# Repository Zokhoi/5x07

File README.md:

# Project 5x07

A low profile ortholinear split keyboard with per-key RGB.

This is a project that began as my first adventure into PCB and keyboard design.

## Parts required

**This table is for one PCB. You need double of this for both hands.**

| Part                                                                                                                                                   | Part Details                                                                                                                                                                        | Quantity | Notes                                       |
| ------------------------------------------------------------------------------------------------------------------------------------------------------ | ----------------------------------------------------------------------------------------------------------------------------------------------------------------------------------- | -------- | ------------------------------------------- |
| [ATmega32u4-AU](https://item.taobao.com/item.htm?id=677430063008)                                                                                      | TQFP-44                                                                                                                                                                             | 1        |                                             |
| [Korean Hroparts Elec TYPE-C-31-M-12](https://www.lcsc.com/product-detail/USB-Type-C_Korean-Hroparts-Elec-TYPE-C-31-M-12_C165948.html)                 |                                                                                                                                                                                     | 1        |                                             |
| [Korean Hroparts ELEC PJ-3200B-4A TRRS Jack](https://www.lcsc.com/product-detail/Audio-Video-Connectors_Korean-Hroparts-Elec-PJ-3200B-4A_C136687.html) |                                                                                                                                                                                     | 1        | For split keyboard connection               |
| [SK6812 Mini-E Reverse Mount LED](https://item.taobao.com/item.htm?id=669061805532)                                                                    |                                                                                                                                                                                     | 35       |                                             |
| [16MHz 3225 SMD Crystal](https://lcsc.com/product-detail/Crystals_Seiko-Epson-X1E000021061300_C255909.html)                                            |                                                                                                                                                                                     | 1        |                                             |
| [PRTR5V0U2X](https://lcsc.com/product-detail/Diodes-ESD_Nexperia-PRTR5V0U2X-215_C12333.html)                                                           | SOT143B                                                                                                                                                                             |          | For ESD protection                          |
| [SKQG push button switch](https://lcsc.com/product-detail/Tactile-Switches_ALPSALPINE-SKQGAFE010_C202424.html)                                         |                                                                                                                                                                                     | 1        | For reset circuit                           |
| 0608/2012 SMD Resistor                                                                                                                                 | [10kΩ](https://lcsc.com/product-detail/Chip-Resistor-Surface-Mount_Viking-Tech-AR05BTCW1002_C316200.html)                                                                           | 3        | For MCU HWB and TRRS jack (i2c)             |
|                                                                                                                                                        | [500Ω](https://lcsc.com/product-detail/Chip-Resistor-Surface-Mount_Viking-Tech-ARG05BTC5000_C2828711.html)                                                                          | 1        | For keyboard LED                            |
|                                                                                                                                                        | [5.1kΩ](https://lcsc.com/product-detail/Chip-Resistor-Surface-Mount_Viking-Tech-AR05DTCW5101_C319564.html)                                                                          | 2        | For USB-C CC                                |
|                                                                                                                                                        | [22Ω](https://lcsc.com/product-detail/Chip-Resistor-Surface-Mount_Viking-Tech-ARG05BTC0220_C309084.html)                                                                            | 2        | For USB-C data                              |
|                                                                                                                                                        | [330Ω](https://lcsc.com/product-detail/Chip-Resistor-Surface-Mount_Viking-Tech-ARG05BTC3300_C2984456.html)                                                                          | 1        | For reset circuit                           |
| 1206/3212 SMD Fuse                                                                                                                                     | [500mA](https://lcsc.com/product-detail/PTC-Resettable-Fuses_TECHFUSE-nSMD025-24V_C70069.html)                                                                                      | 1        |                                             |
| Diodes                                                                                                                                                 | [1N4148](https://lcsc.com/product-detail/Switching-Diode_MCC-Micro-Commercial-Components-1N4148W-TP_C77978.html) or SMD                                                             | 35       | For keyboard matrix                         |
|                                                                                                                                                        | [Schottky](https://lcsc.com/product-detail/Schottky-Barrier-Diodes-SBD_Shikues-B5817WL_C122853.html)                                                                                | 1        | For USB-C power                             |
| 0805 SMD Capacitors                                                                                                                                    | [22 pF](https://lcsc.com/product-detail/Multilayer-Ceramic-Capacitors-MLCC-SMD-SMT_Samsung-Electro-Mechanics-CL21C220JCANNNC_C165459.html)                                          | 2        | For crystal                                 |
|                                                                                                                                                        | [1 uF](https://lcsc.com/product-detail/Multilayer-Ceramic-Capacitors-MLCC-SMD-SMT_Samsung-Electro-Mechanics_CL21B105KAFNNNE_Samsung-Electro-Mechanics-CL21B105KAFNNNE_C116352.html) | 1        | For MCU UCAP                                |
|                                                                                                                                                        | [10 uF](https://lcsc.com/product-detail/Multilayer-Ceramic-Capacitors-MLCC-SMD-SMT_SAMSUNG_CL21B106KOQNNNE_10uF-106-10-16V_C95841.html)                                             | 1        | For decoupling                              |
|                                                                                                                                                        | [0.1 uF](https://lcsc.com/product-detail/Multilayer-Ceramic-Capacitors-MLCC-SMD-SMT_SAMSUNG_CL21B104JBCNNNC_100nF-104-5-50V_C62912.html)                                            | 4        | For decoupling                              |
| M2 screws                                                                                                                                              | >=3mm                                                                                                                                                                               | 8        | For bottom plate, length for reference only |
| M2 standoff                                                                                                                                            | 3mm                                                                                                                                                                                 | 4        | For bottom plate, length for reference only |

## Board details

Fabrication gerber files are in `./PCB/gerber` directory.

103.188 mm H x 168.275 mm W <br />
2 layers <br />
Unleaded HASL or ENIG <br />
1.6mm thick <br />
white on black

## Assembly instructions

The images below are PCBs for v3.

The board is designed to be reversible. You can flip the PCB to the other side to serve as the other half.

The parts that are mountable on both sides of the PCB are the type C port, the TRRS jack, the reset button and the key matrix (switch, LED, diode).

The side for mounting type C port and TRRS jack is up to your will. The reset button should always face up for ease of access. The LEDs for keyboard are reverse mounted. Key diodes should be on the underside.

As one side would have its electrionic components mostly facing down, you should lift the split halves up to avoid shorting. If you have leftover boards from ordering in batch amounts, it is possible to use them as bottom plates using M2 screws and standoffs. 

For information, the shortest M2 standoffs I can find are 3mm in length, the type C port is 3.2mm high, and the TRRS jack is 5mm high (the outer plastic ring might be 5.6mm high). If you decide to put the type C port and TRRS jack on the top side, you can have the standoff as short as just higher than the electronic components on the board.

## Build instructions

By default the keyboard is set to use EEPROM handedness check, this means that
for the first time for both halves the following commands need to be used:

```bash
make 5x07:default:dfu-split-left
make 5x07:default:dfu-split-right
```

afterwards the end part can be dropped when flashing again.

For v3 and below there is no VBUS detection, so USB activity detection must be used for split master detection if you do not want to hardcode the master half. <br />
V3.1 onwards has VBUS detection and you can use it normally.

## CAUTIONS

I couldn't for the life of me figure out how to stably enable the per key RGB, so use at your own risk.

Some problems that I encountered were:

* RHS board (using EEPROM flags) could have RGB lights on in QMK, but then it disconnects if the mode switches from the static gradient to static solid color.
* RHS board can change modes between different static gradients if its hue/saturation/value are turned down first.
* LHS board disconnects from computer immediately after connection when RGB is enabled. If the USB is connected to RHS board and LHS is connected to RHS via i2c, it would drag both halves down with the disconnection. After disconnection, the RGB lights start to flicker.
* RHS board would also display random disconnection behavior if the hsv are changed too fast.

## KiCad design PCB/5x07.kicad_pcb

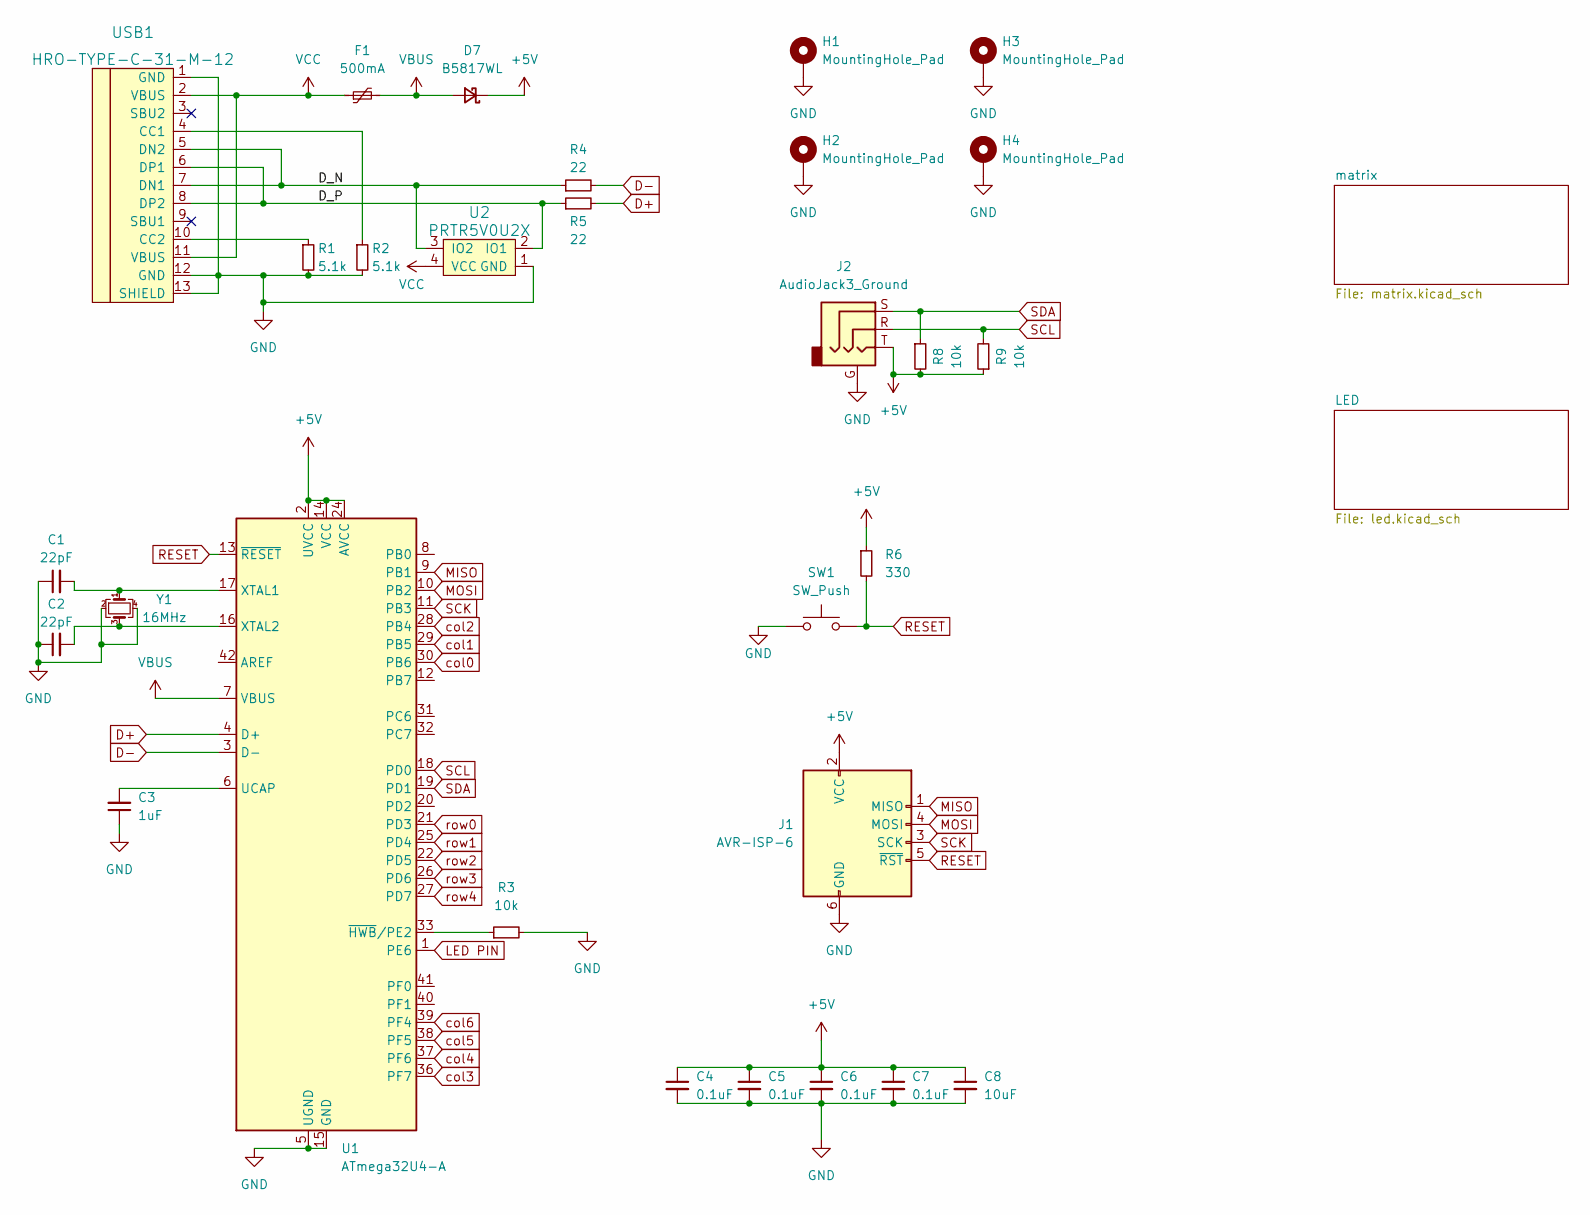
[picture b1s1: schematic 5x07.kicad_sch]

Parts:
C1, C2: 22pF; C_0805_2012Metric_Pad1.18x1.45mm_HandSolder
C3: 1uF; C_0805_2012Metric_Pad1.18x1.45mm_HandSolder
C4, C5, C6, C7: 0.1uF; C_0805_2012Metric_Pad1.18x1.45mm_HandSolder
C8: 10uF; C_0805_2012Metric_Pad1.18x1.45mm_HandSolder
D7: B5817WL; D_SOD-123F
F1: 500mA; Fuse_1206_3216Metric_Pad1.42x1.75mm_HandSolder
H1, H2, H3, H4: MountingHole_Pad; Generic-Mounthole
J1: AVR-ISP-6; Reset_Pretty
J2: AudioJack3_Ground; PJ-3200B-4A-Reversible-Mini
R1, R2: 5.1k; R_0805_2012Metric_Pad1.20x1.40mm_HandSolder
R3, R8, R9: 10k; R_0805_2012Metric_Pad1.20x1.40mm_HandSolder
R4, R5: 22; R_0805_2012Metric_Pad1.20x1.40mm_HandSolder
R6: 330; R_0805_2012Metric_Pad1.20x1.40mm_HandSolder
SW1: SW_Push; SW_SPST_SKQG_WithStem_Reversible
U1: ATmega32U4-A; TQFP-44_10x10mm_P0.8mm
U2: PRTR5V0U2X; SOT143B
USB1: HRO-TYPE-C-31-M-12; HRO-TYPE-C-31-M-12-HandSoldering-Reversible
Y1: 16MHz; Crystal_SMD_3225-4Pin_3.2x2.5mm_HandSoldering

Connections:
+5V: C4.1, C5.1, C6.1, C7.1, C8.1, D7.1 (K), J1.2 (VCC), J2.T, R6.1, R8.2, R9.1, U1.2 (UVCC), U1.14 (VCC), U1.24 (AVCC), U1.34 (VCC), U1.44 (AVCC); also elsewhere on the board
/D_N: R4.1, U2.3 (IO2), USB1.5 (DN2), USB1.7 (DN1)
/D_P: R5.1, U2.2 (IO1), USB1.6 (DP1), USB1.8 (DP2)
D+: R5.2, U1.4 (D+)
D-: R4.2, U1.3 (D-)
GND: C1.1, C2.1, C3.1, C4.2, C5.2, C6.2, C7.2, C8.2, H1.1, H2.1, H3.1, H4.1, J1.6 (GND), J2.G, R1.2, R2.2, R3.2, SW1.1, U1.5 (UGND), U1.15 (GND), U1.23 (GND), U1.35 (GND), U1.43 (GND), U2.1 (GND), USB1.1 (GND), USB1.12 (GND), USB1.13 (SHIELD), Y1.2, Y1.4; also elsewhere on the board
LED PIN: U1.1 (PE6); also elsewhere on the board
MISO: J1.1 (MISO), U1.9 (PB1)
MOSI: J1.4 (MOSI), U1.10 (PB2)
unnamed: C1.2, U1.17 (XTAL1), Y1.1
unnamed: C2.2, U1.16 (XTAL2), Y1.3
unnamed: C3.2, U1.6 (UCAP)
unnamed: R1.1, USB1.10 (CC2)
unnamed: R2.1, USB1.4 (CC1)
unnamed: R3.1, U1.33 (~HWB/PE2)
RESET: J1.5 (~RST), R6.2, SW1.2, U1.13 (~RESET)
SCK: J1.3 (SCK), U1.11 (PB3)
SCL: J2.R, R9.2, U1.18 (PD0)
SDA: J2.S, R8.1, U1.19 (PD1)
VCC: F1.1, U2.4 (VCC), USB1.2 (VBUS), USB1.11 (VBUS)
col0: U1.30 (PB6); also elsewhere on the board
col1: U1.29 (PB5); also elsewhere on the board
col2: U1.28 (PB4); also elsewhere on the board
col3: U1.36 (PF7); also elsewhere on the board
col4: U1.37 (PF6); also elsewhere on the board
col5: U1.38 (PF5); also elsewhere on the board
col6: U1.39 (PF4); also elsewhere on the board
row0: U1.21 (PD3); also elsewhere on the board
row1: U1.25 (PD4); also elsewhere on the board
row2: U1.22 (PD5); also elsewhere on the board
row3: U1.26 (PD6); also elsewhere on the board
row4: U1.27 (PD7); also elsewhere on the board

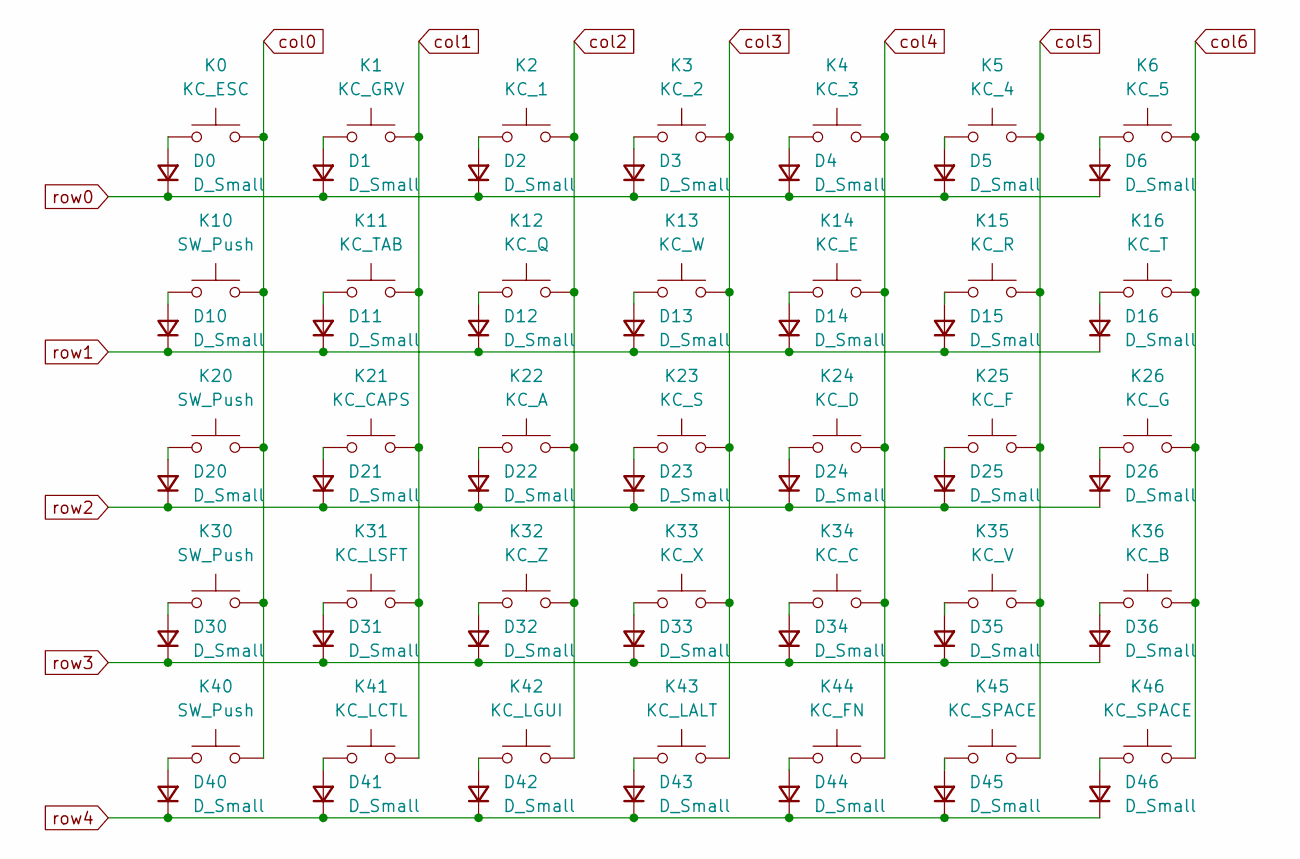
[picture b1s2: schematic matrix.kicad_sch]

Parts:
D0, D1, D2, D3, D4, D5, D6, D10, D11, D12, D13, D14, D15, D16, D20, D21, D22, D23, D24, D25, D26, D30, D31, D32, D33, D34, D35, D36, D40, D41, D42, D43, D44, D45, D46: D_Small; D_SOD-123-Reversible
K0: KC_ESC; SW_choc_1u_reversible
K1: KC_GRV; SW_choc_1u_reversible
K2: KC_1; SW_choc_1u_reversible
K3: KC_2; SW_choc_1u_reversible
K4: KC_3; SW_choc_1u_reversible
K5: KC_4; SW_choc_1u_reversible
K6: KC_5; SW_choc_1u_reversible
K10, K20, K30, K40: SW_Push; SW_choc_1u_reversible
K11: KC_TAB; SW_choc_1u_reversible
K12: KC_Q; SW_choc_1u_reversible
K13: KC_W; SW_choc_1u_reversible
K14: KC_E; SW_choc_1u_reversible
K15: KC_R; SW_choc_1u_reversible
K16: KC_T; SW_choc_1u_reversible
K21: KC_CAPS; SW_choc_1u_reversible
K22: KC_A; SW_choc_1u_reversible
K23: KC_S; SW_choc_1u_reversible
K24: KC_D; SW_choc_1u_reversible
K25: KC_F; SW_choc_1u_reversible
K26: KC_G; SW_choc_1u_reversible
K31: KC_LSFT; SW_choc_1u_reversible
K32: KC_Z; SW_choc_1u_reversible
K33: KC_X; SW_choc_1u_reversible
K34: KC_C; SW_choc_1u_reversible
K35: KC_V; SW_choc_1u_reversible
K36: KC_B; SW_choc_1u_reversible
K41: KC_LCTL; SW_choc_1u_reversible
K42: KC_LGUI; SW_choc_1u_reversible
K43: KC_LALT; SW_choc_1u_reversible
K44: KC_FN; SW_choc_1u_reversible
K45, K46: KC_SPACE; SW_choc_1u_reversible

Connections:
unnamed: D0.2 (A), K0.1
unnamed: D1.2 (A), K1.1
unnamed: D2.2 (A), K2.1
unnamed: D3.2 (A), K3.1
unnamed: D4.2 (A), K4.1
unnamed: D5.2 (A), K5.1
unnamed: D6.2 (A), K6.1
unnamed: D10.2 (A), K10.1
unnamed: D11.2 (A), K11.1
unnamed: D12.2 (A), K12.1
unnamed: D13.2 (A), K13.1
unnamed: D14.2 (A), K14.1
unnamed: D15.2 (A), K15.1
unnamed: D16.2 (A), K16.1
unnamed: D20.2 (A), K20.1
unnamed: D21.2 (A), K21.1
unnamed: D22.2 (A), K22.1
unnamed: D23.2 (A), K23.1
unnamed: D24.2 (A), K24.1
unnamed: D25.2 (A), K25.1
unnamed: D26.2 (A), K26.1
unnamed: D30.2 (A), K30.1
unnamed: D31.2 (A), K31.1
unnamed: D32.2 (A), K32.1
unnamed: D33.2 (A), K33.1
unnamed: D34.2 (A), K34.1
unnamed: D35.2 (A), K35.1
unnamed: D36.2 (A), K36.1
unnamed: D40.2 (A), K40.1
unnamed: D41.2 (A), K41.1
unnamed: D42.2 (A), K42.1
unnamed: D43.2 (A), K43.1
unnamed: D44.2 (A), K44.1
unnamed: D45.2 (A), K45.1
unnamed: D46.2 (A), K46.1
col0: K0.2, K10.2, K20.2, K30.2, K40.2; also elsewhere on the board
col1: K1.2, K11.2, K21.2, K31.2, K41.2; also elsewhere on the board
col2: K2.2, K12.2, K22.2, K32.2, K42.2; also elsewhere on the board
col3: K3.2, K13.2, K23.2, K33.2, K43.2; also elsewhere on the board
col4: K4.2, K14.2, K24.2, K34.2, K44.2; also elsewhere on the board
col5: K5.2, K15.2, K25.2, K35.2, K45.2; also elsewhere on the board
col6: K6.2, K16.2, K26.2, K36.2, K46.2; also elsewhere on the board
row0: D0.1 (K), D1.1 (K), D2.1 (K), D3.1 (K), D4.1 (K), D5.1 (K), D6.1 (K); also elsewhere on the board
row1: D10.1 (K), D11.1 (K), D12.1 (K), D13.1 (K), D14.1 (K), D15.1 (K), D16.1 (K); also elsewhere on the board
row2: D20.1 (K), D21.1 (K), D22.1 (K), D23.1 (K), D24.1 (K), D25.1 (K), D26.1 (K); also elsewhere on the board
row3: D30.1 (K), D31.1 (K), D32.1 (K), D33.1 (K), D34.1 (K), D35.1 (K), D36.1 (K); also elsewhere on the board
row4: D40.1 (K), D41.1 (K), D42.1 (K), D43.1 (K), D44.1 (K), D45.1 (K), D46.1 (K); also elsewhere on the board

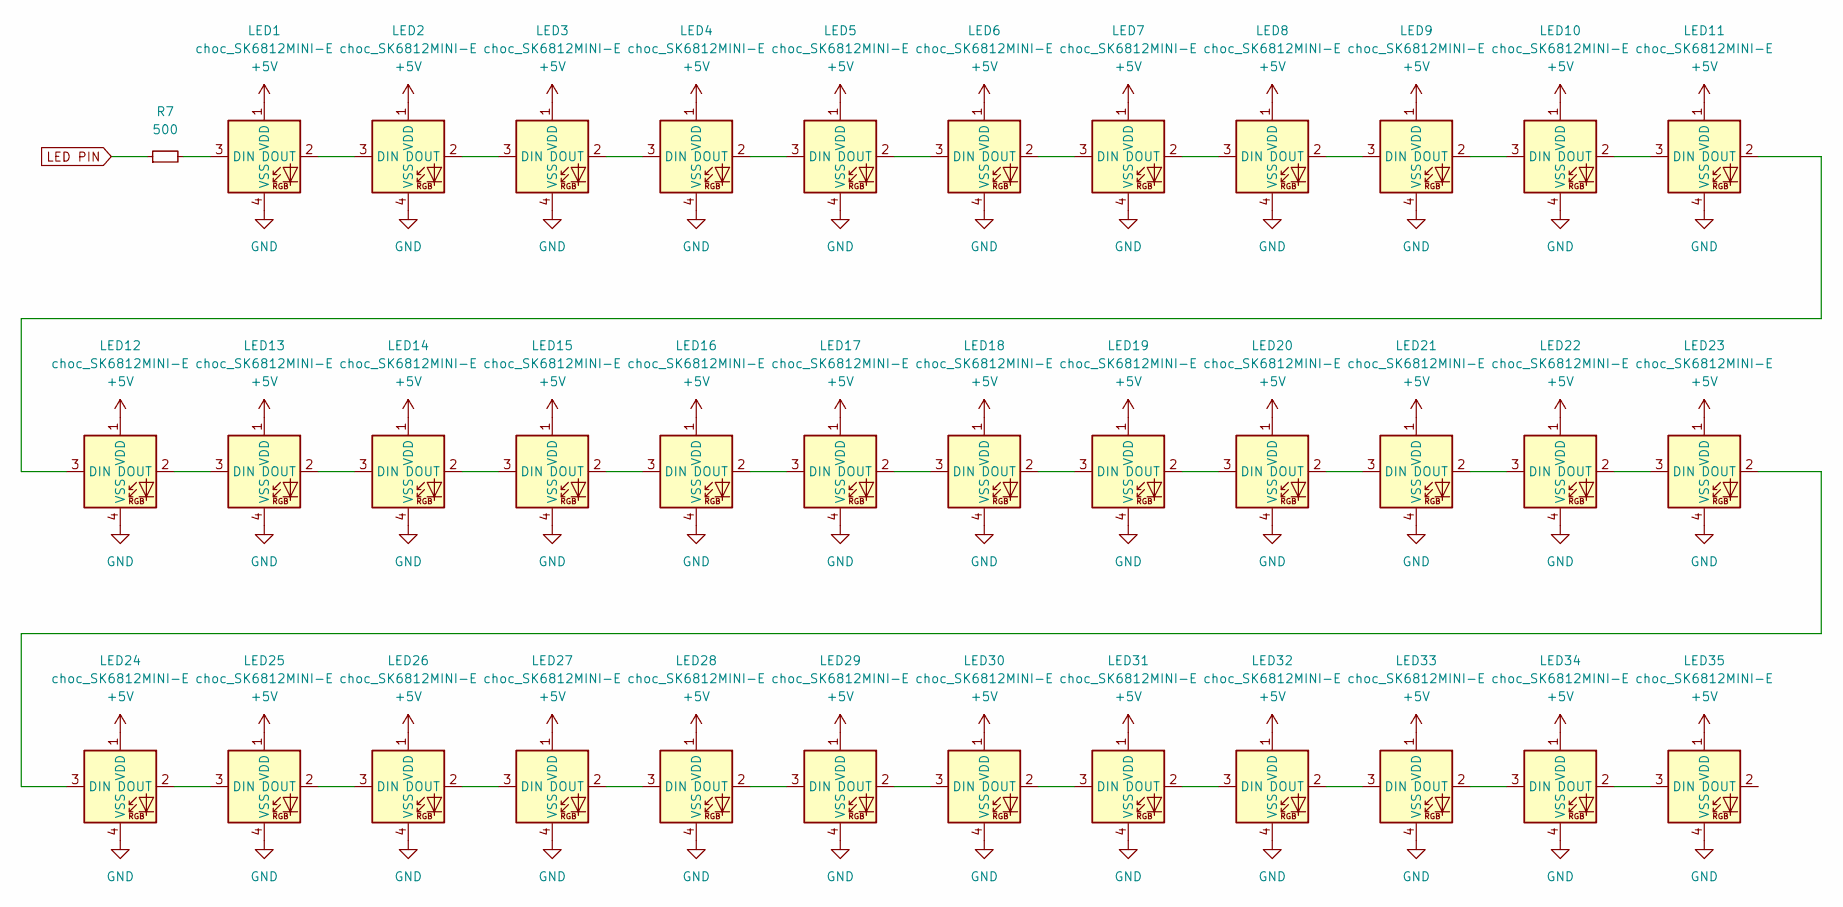
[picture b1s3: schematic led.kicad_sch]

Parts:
LED1, LED2, LED3, LED4, LED5, LED6, LED7, LED8, LED9, LED10, LED11, LED12, LED13, LED14, LED15, LED16, LED17, LED18, LED19, LED20, LED21, LED22, LED23, LED24, LED25, LED26, LED27, LED28, LED29, LED30, LED31, LED32, LED33, LED34, LED35: choc_SK6812MINI-E; LED_choc_6028R_Reversible_same_side
R7: 500; R_0805_2012Metric_Pad1.20x1.40mm_HandSolder

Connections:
+5V: LED1.1 (VDD), LED2.1 (VDD), LED3.1 (VDD), LED4.1 (VDD), LED5.1 (VDD), LED6.1 (VDD), LED7.1 (VDD), LED8.1 (VDD), LED9.1 (VDD), LED10.1 (VDD), LED11.1 (VDD), LED12.1 (VDD), LED13.1 (VDD), LED14.1 (VDD), LED15.1 (VDD), LED16.1 (VDD), LED17.1 (VDD), LED18.1 (VDD), LED19.1 (VDD), LED20.1 (VDD), LED21.1 (VDD), LED22.1 (VDD), LED23.1 (VDD), LED24.1 (VDD), LED25.1 (VDD), LED26.1 (VDD), LED27.1 (VDD), LED28.1 (VDD), LED29.1 (VDD), LED30.1 (VDD), LED31.1 (VDD), LED32.1 (VDD), LED33.1 (VDD), LED34.1 (VDD), LED35.1 (VDD); also elsewhere on the board
GND: LED1.4 (VSS), LED2.4 (VSS), LED3.4 (VSS), LED4.4 (VSS), LED5.4 (VSS), LED6.4 (VSS), LED7.4 (VSS), LED8.4 (VSS), LED9.4 (VSS), LED10.4 (VSS), LED11.4 (VSS), LED12.4 (VSS), LED13.4 (VSS), LED14.4 (VSS), LED15.4 (VSS), LED16.4 (VSS), LED17.4 (VSS), LED18.4 (VSS), LED19.4 (VSS), LED20.4 (VSS), LED21.4 (VSS), LED22.4 (VSS), LED23.4 (VSS), LED24.4 (VSS), LED25.4 (VSS), LED26.4 (VSS), LED27.4 (VSS), LED28.4 (VSS), LED29.4 (VSS), LED30.4 (VSS), LED31.4 (VSS), LED32.4 (VSS), LED33.4 (VSS), LED34.4 (VSS), LED35.4 (VSS); also elsewhere on the board
LED PIN: R7.1; also elsewhere on the board
unnamed: LED1.2 (DOUT), LED2.3 (DIN)
unnamed: LED1.3 (DIN), R7.2
unnamed: LED2.2 (DOUT), LED3.3 (DIN)
unnamed: LED3.2 (DOUT), LED4.3 (DIN)
unnamed: LED4.2 (DOUT), LED5.3 (DIN)
unnamed: LED5.2 (DOUT), LED6.3 (DIN)
unnamed: LED6.2 (DOUT), LED7.3 (DIN)
unnamed: LED7.2 (DOUT), LED8.3 (DIN)
unnamed: LED8.2 (DOUT), LED9.3 (DIN)
unnamed: LED10.2 (DOUT), LED11.3 (DIN)
unnamed: LED9.2 (DOUT), LED10.3 (DIN)
unnamed: LED11.2 (DOUT), LED12.3 (DIN)
unnamed: LED12.2 (DOUT), LED13.3 (DIN)
unnamed: LED13.2 (DOUT), LED14.3 (DIN)
unnamed: LED14.2 (DOUT), LED15.3 (DIN)
unnamed: LED15.2 (DOUT), LED16.3 (DIN)
unnamed: LED16.2 (DOUT), LED17.3 (DIN)
unnamed: LED17.2 (DOUT), LED18.3 (DIN)
unnamed: LED18.2 (DOUT), LED19.3 (DIN)
unnamed: LED19.2 (DOUT), LED20.3 (DIN)
unnamed: LED20.2 (DOUT), LED21.3 (DIN)
unnamed: LED21.2 (DOUT), LED22.3 (DIN)
unnamed: LED22.2 (DOUT), LED23.3 (DIN)
unnamed: LED23.2 (DOUT), LED24.3 (DIN)
unnamed: LED24.2 (DOUT), LED25.3 (DIN)
unnamed: LED25.2 (DOUT), LED26.3 (DIN)
unnamed: LED26.2 (DOUT), LED27.3 (DIN)
unnamed: LED27.2 (DOUT), LED28.3 (DIN)
unnamed: LED28.2 (DOUT), LED29.3 (DIN)
unnamed: LED29.2 (DOUT), LED30.3 (DIN)
unnamed: LED30.2 (DOUT), LED31.3 (DIN)
unnamed: LED31.2 (DOUT), LED32.3 (DIN)
unnamed: LED32.2 (DOUT), LED33.3 (DIN)
unnamed: LED33.2 (DOUT), LED34.3 (DIN)
unnamed: LED34.2 (DOUT), LED35.3 (DIN)

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
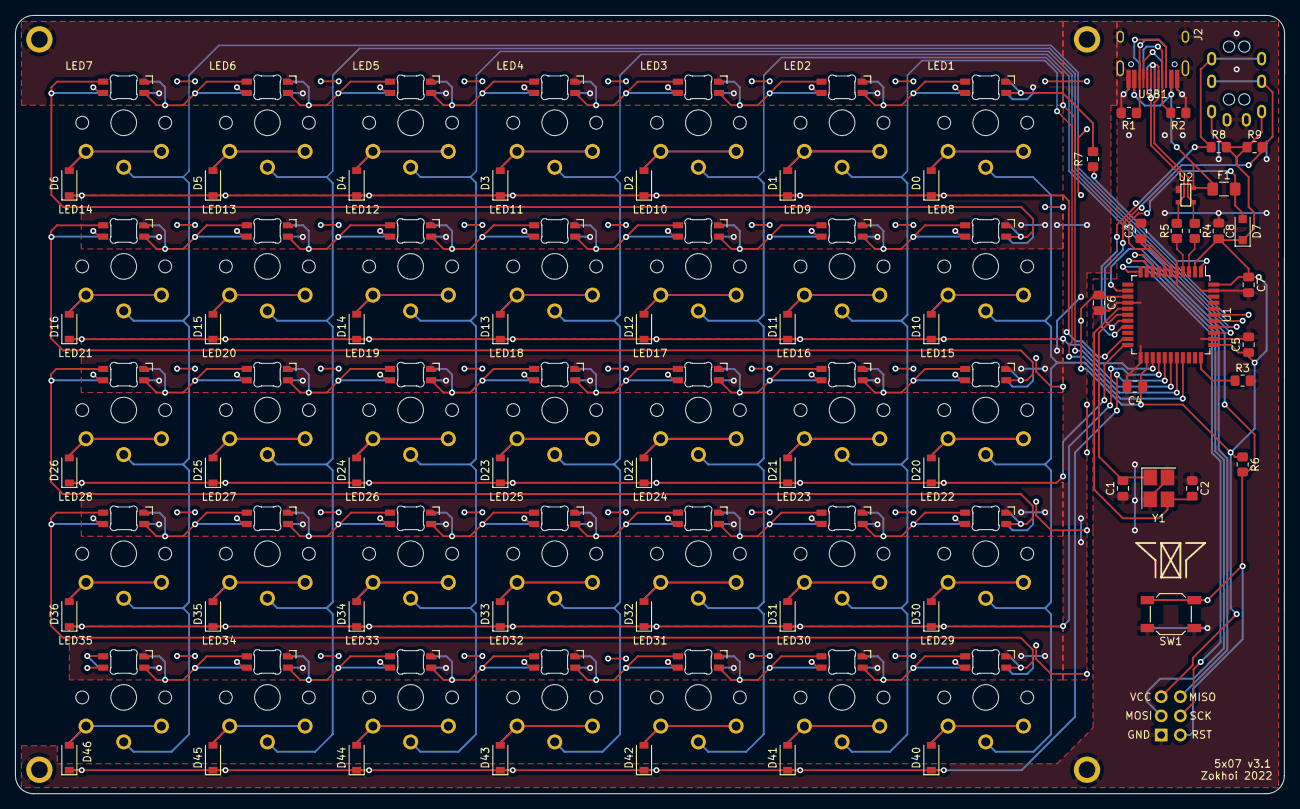
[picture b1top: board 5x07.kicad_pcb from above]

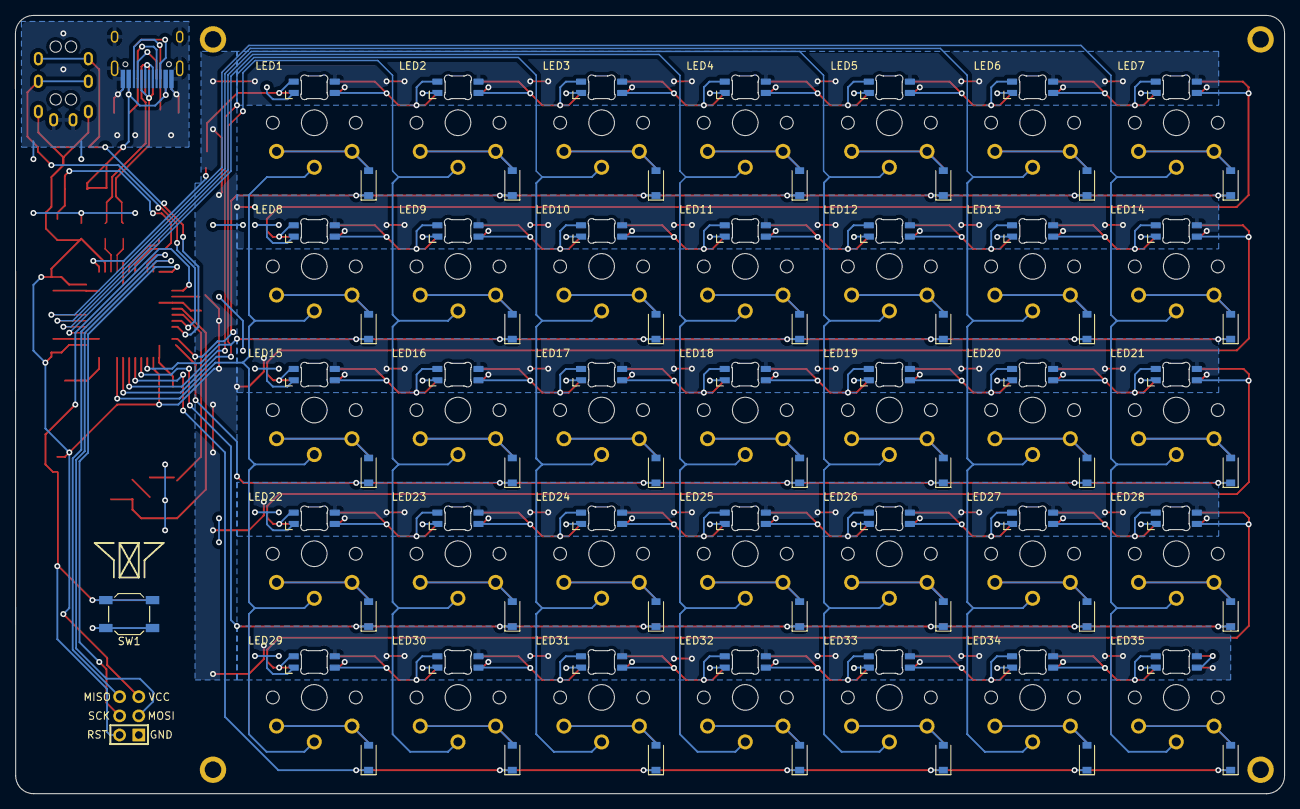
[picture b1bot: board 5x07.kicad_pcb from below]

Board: 2 copper layers, 168.3 x 103.2 mm, 135 parts (37 on the bottom side), 103 nets.

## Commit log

2022-08-05 init: v1
2022-08-06 v2: reversiblility for LHS and RHS
2022-08-06 bugfixes, doc and logo
2022-08-06 v3: TRRS for split sides
2022-08-06 backport bugfix from v3
2022-08-07 bugfix
2022-08-11 minified TRRS jack footprint and other bugfixes
2022-09-04 added build pics and instructions
2022-09-04 added v3 alpha firmware
2022-09-05 Fix dot and comma
2022-09-10 add equal key
2022-09-10 added vbus detection compatibility
2022-09-19 minor update
